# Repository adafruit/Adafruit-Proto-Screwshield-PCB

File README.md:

# Proto-Screwshield (Wingshield) R3 Kit for Arduino

<a href="http://www.adafruit.com/products/196"><br/>
Click here to purchase one from the Adafruit shop
</a>

The next generation Proto-ScrewShield is a dual-purpose prototyping shield. Not only does it have a large 0.1" grid prototyping area but it also extends the Arduino pins to sturdy, secure, and dependable screw terminal blocks. You even get a few bonus terminals for extra GND and four 'free' terminals for whatever connections you wish! __New! As of June 23, 2014 we now have an R3 update to this design__ - we now have a stacking header for the ICSP 2x3 pins and breakout the SCL and SDA pins. It now works much better with R3 UNO's, Mega, Leonardo, as well as stacking nicely with any shield.

The stack-able wing design allows you slip this under any shield and still get easy access to the "analog" & "digital" ports of the Arduino. The ScrewShield can be stacked above or below pretty much every other shield.

- 1 large high-quality PCB, specifically chosen for its excellent resistance to lots of soldering and desoldering (essential for prototyping boards)
- Plenty of prototyping space, with power/ground rails
- Diffused green power LED, extra diffused red LED for user choice (although we suggest to connect it to pin 13)
- Reset button
- Full set of stacking female header pins
- Lots of 3.5mm terminal blocks to fill 36 breakouts on the board

### License

Adafruit invests time and resources providing this open source design, please support Adafruit and open-source hardware by purchasing products from [Adafruit](https://www.adafruit.com)!

Designed by Limor Fried/Ladyada for Adafruit Industries.

Creative Commons Attribution/Share-Alike, all text above must be included in any redistribution. See license.txt for additional details.

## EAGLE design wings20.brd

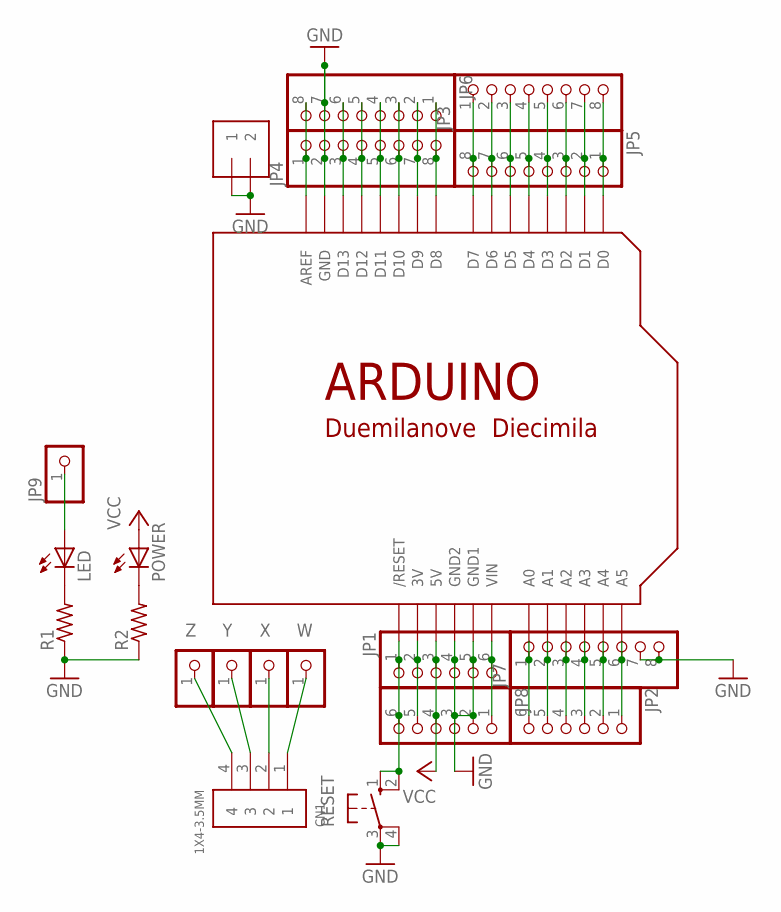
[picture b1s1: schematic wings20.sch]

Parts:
CN1: 1X4-3.5MM; 1X04-3.5MM
J1: 1X2-3.5MM
JP1: PINHD-1X6-3.5MM; 1X06-3.5MM
JP2, JP8: PINHD-1X6CB; 1X06-CLEANBIG
JP3, JP4: PINHD-1X8CLEANBIG; 1X08-CLEANBIG
JP5, JP6, JP7: PINHD-1X8-3.5MM; 1X08-3.5MM
JP9: PINHD-1X1; 1X01
LED: LED3MM
POWER: LED3MM
R1, R2: R-US_0207/10; 0207/10
RESET: 10-XX; B3F-10XX
U$1: ARDUINO-BPLACE
W: PINHD-1X1; 1X01
X: PINHD-1X1; 1X01
Y: PINHD-1X1; 1X01
Z: PINHD-1X1; 1X01

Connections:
3V: JP1.2, JP8.5, U$1.3V
GND: J1.1, J1.2, JP1.4, JP1.5, JP4.2, JP6.7, JP7.7, JP7.8, JP8.2, JP8.3, R1.1, R2.1, RESET.3, RESET.4 (P1), U$1.GND, U$1.GND1, U$1.GND2
unnamed: JP3.1, JP5.8, U$1.D7
unnamed: JP3.2, JP5.7, U$1.D6
unnamed: JP3.3, JP5.6, U$1.D5
unnamed: JP3.4, JP5.5, U$1.D4
unnamed: JP3.5, JP5.4, U$1.D3
unnamed: JP3.6, JP5.3, U$1.D2
unnamed: JP3.7, JP5.2, U$1.D1
unnamed: JP3.8, JP5.1, U$1.D0
unnamed: JP4.1, JP6.8, U$1.AREF
unnamed: LED.K (C), R1.2
unnamed: JP4.3, JP6.6, U$1.D13
unnamed: JP4.4, JP6.5, U$1.D12
unnamed: JP4.5, JP6.4, U$1.D11
unnamed: JP4.6, JP6.3, U$1.D10
unnamed: JP4.7, JP6.2, U$1.D9
unnamed: JP4.8, JP6.1, U$1.D8
unnamed: JP2.1, JP7.6, U$1.A5
unnamed: JP2.2, JP7.5, U$1.A4
unnamed: JP2.3, JP7.4, U$1.A3
unnamed: JP2.4, JP7.3, U$1.A2
unnamed: JP2.5, JP7.2, U$1.A1
unnamed: JP2.6, JP7.1, U$1.A0
unnamed: POWER.K (C), R2.2
unnamed: JP9.1, LED.A
unnamed: CN1.4, Z.1
unnamed: JP1.1, JP8.6, RESET.1 (S), RESET.2 (S1), U$1.RESET (/RESET)
unnamed: CN1.3, Y.1
unnamed: CN1.2, X.1
unnamed: CN1.1, W.1
VCC: JP1.3, JP8.4, POWER.A, U$1.5V
VIN: JP1.6, JP8.1, U$1.VIN

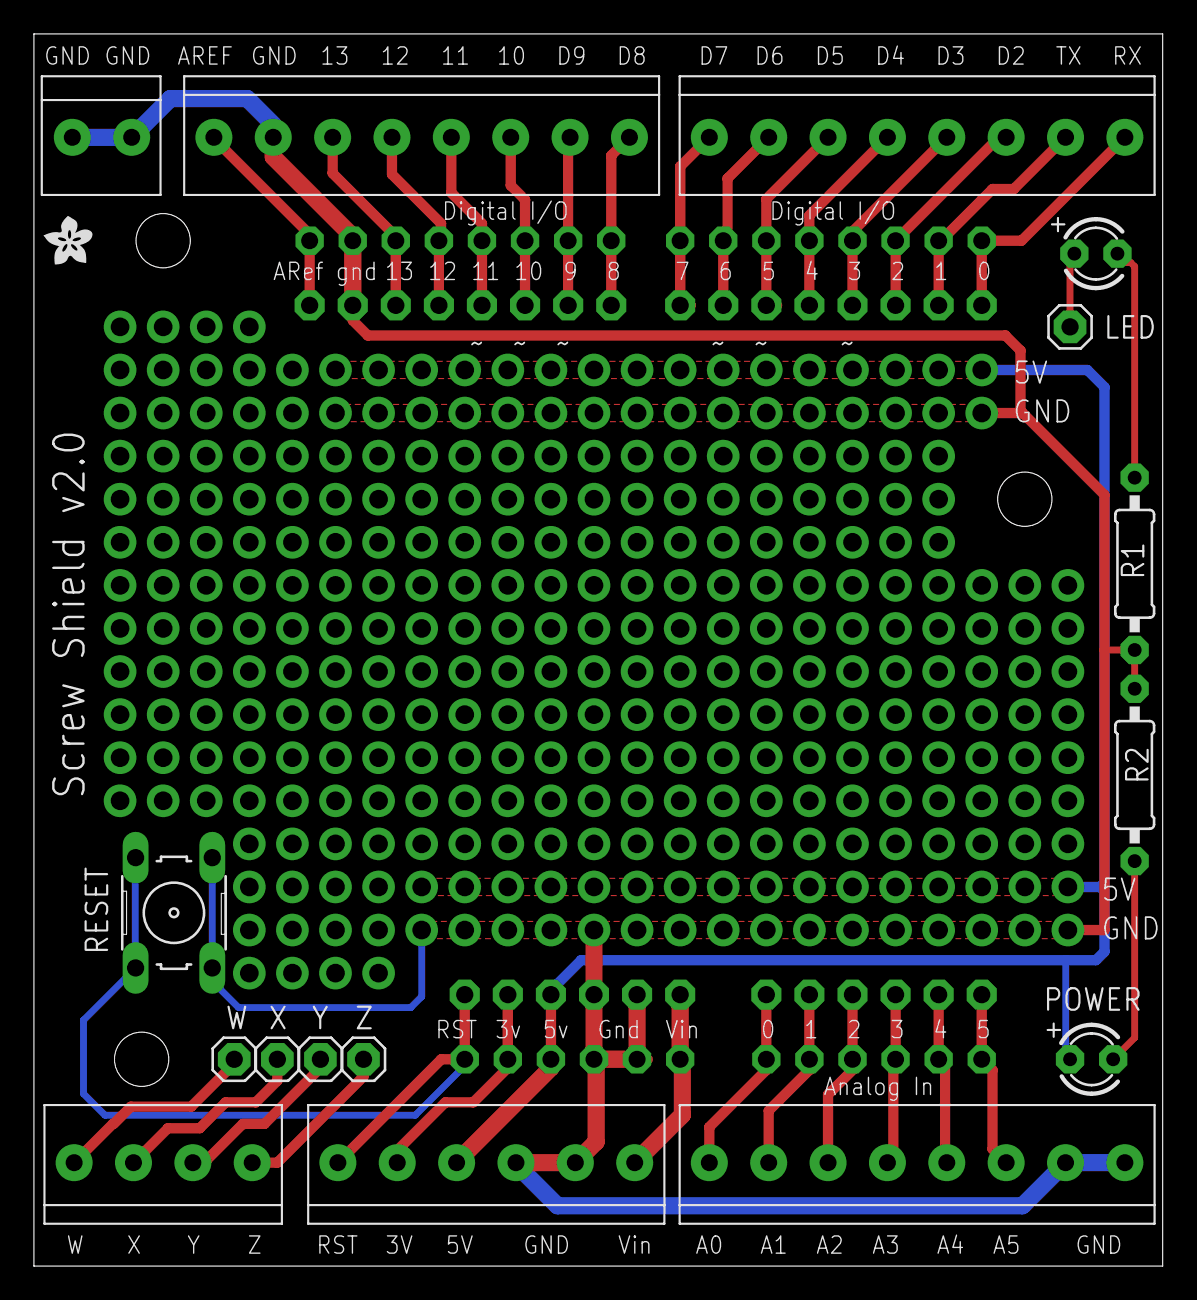
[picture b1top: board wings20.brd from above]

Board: 2 copper layers, 66.5 x 72.6 mm, 22 parts (0 on the bottom side), 33 nets.

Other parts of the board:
U$2: ADAFRUIT200MIL

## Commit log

2011-01-12 initial commit of v2.0 proto
2011-01-20 added breakouts for WXYZ and top silk name
2011-01-21 Fixed Uno spacing (was off a little!)
2011-01-21 fixed uno spacing
2019-03-15 readme + image
2026-04-09 update file format to XML
